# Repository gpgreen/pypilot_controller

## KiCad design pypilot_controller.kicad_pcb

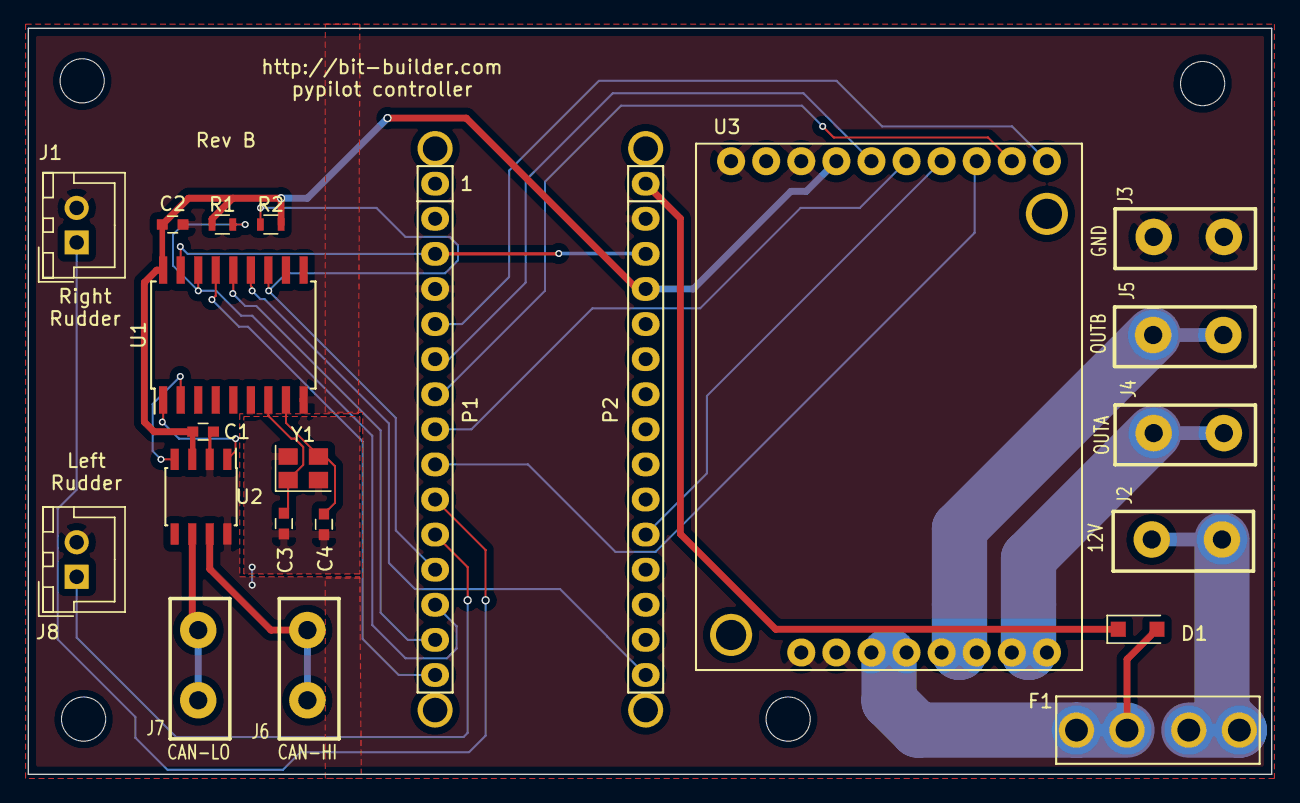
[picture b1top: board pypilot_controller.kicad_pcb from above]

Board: 2 copper layers, 90.0 x 54.0 mm, 30 parts (0 on the bottom side), 27 nets.

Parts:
C1, C2: 0.1uF; C_0603
C3, C4: 18pF; C_0603
D1: PMEG3020EH; D_SOD-123F
F1: 15A; atm_fuse_holder-mpd-bk-6013
H6, H7, H8, H9: MountingHole; MountingHole_3.2mm_M3
J1: Right Rudder Stop; JST_XH_B02B-XH-A_02x2.50mm_Straight
J2: 12V; FASTON-187-vert-90deg-terminal
J3: GND; FASTON-187-vert-90deg-terminal
J4: OUTA; FASTON-187-vert-90deg-terminal
J5: OUTB; FASTON-187-vert-90deg-terminal
J6: CAN-HI; FASTON-187-vert-90deg-terminal
J7: CAN-LO; FASTON-187-vert-90deg-terminal
J8: Left Rudder Stop; JST_XH_B02B-XH-A_02x2.50mm_Straight
P1: Digital; Socket_Strip_Arduino_1x15
P2: Analog; Socket_Strip_Arduino_1x15
P3, P4, P5, P6: CONN_01X01; 1pin_Nano
R1, R2: 10K; R_0603
U1: MCP2515-xSO; SOIC-18W_7.5x11.6mm_Pitch1.27mm
U2: MCP2551-I-SN; SOIC-8_3.9x4.9mm_Pitch1.27mm
U3: VNH5019Carrier; VNH5019_Motor_Driver
Y1: 16MHz; Crystal_SMD_TXC_7M-4pin_3.2x2.5mm

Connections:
+5V: C1.1, C2.1, P2.4, R1.1, R2.2, U1.18, U2.3, U3.7
+12V: D1.2, F1.2, U3.13
/Vin: D1.1, P2.1
A1: P2.11, U3.4
CANH: J6.1, U2.7
CANL: J7.1, U2.6
CS: P1.13, R1.2, U1.16
D2: P1.5, U3.1
D3: P1.6, U3.6
D4: P1.7, U3.2
D5: P1.8, U3.5
D6: P1.9, U3.3
D7: J1.1, P1.10
D8: J8.1, P1.11
GND: C1.2, C2.2, C3.2, C4.2, J1.2, J3.1, J8.2, P1.4, P2.2, U1.9, U2.2, U2.8, U3.8, U3.10, U3.14, Y1.2, Y1.4
INT: P1.12, R2.1, U1.12
unnamed: C3.1, U1.7, Y1.1
unnamed: C4.1, U1.8, Y1.3
unnamed: F1.1, J2.1
unnamed: U1.1, U2.1
unnamed: U1.2, U2.4
OUTA: J4.1, U3.11
OUTB: J5.1, U3.12
Reset: P1.3, P2.3, U1.17
SCK: P2.15, U1.13
SI: P1.14, U1.14
SO: P1.15, U1.15

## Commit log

2021-04-11 Original commit
2021-04-12 many changes
2021-04-24 Crystal was wired incorrectly
    Replaced schematic symbol
    Fixed pcb layout
    incremented revision to B
